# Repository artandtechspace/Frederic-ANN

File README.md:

# Frederic-ANN
Analog Neural Network

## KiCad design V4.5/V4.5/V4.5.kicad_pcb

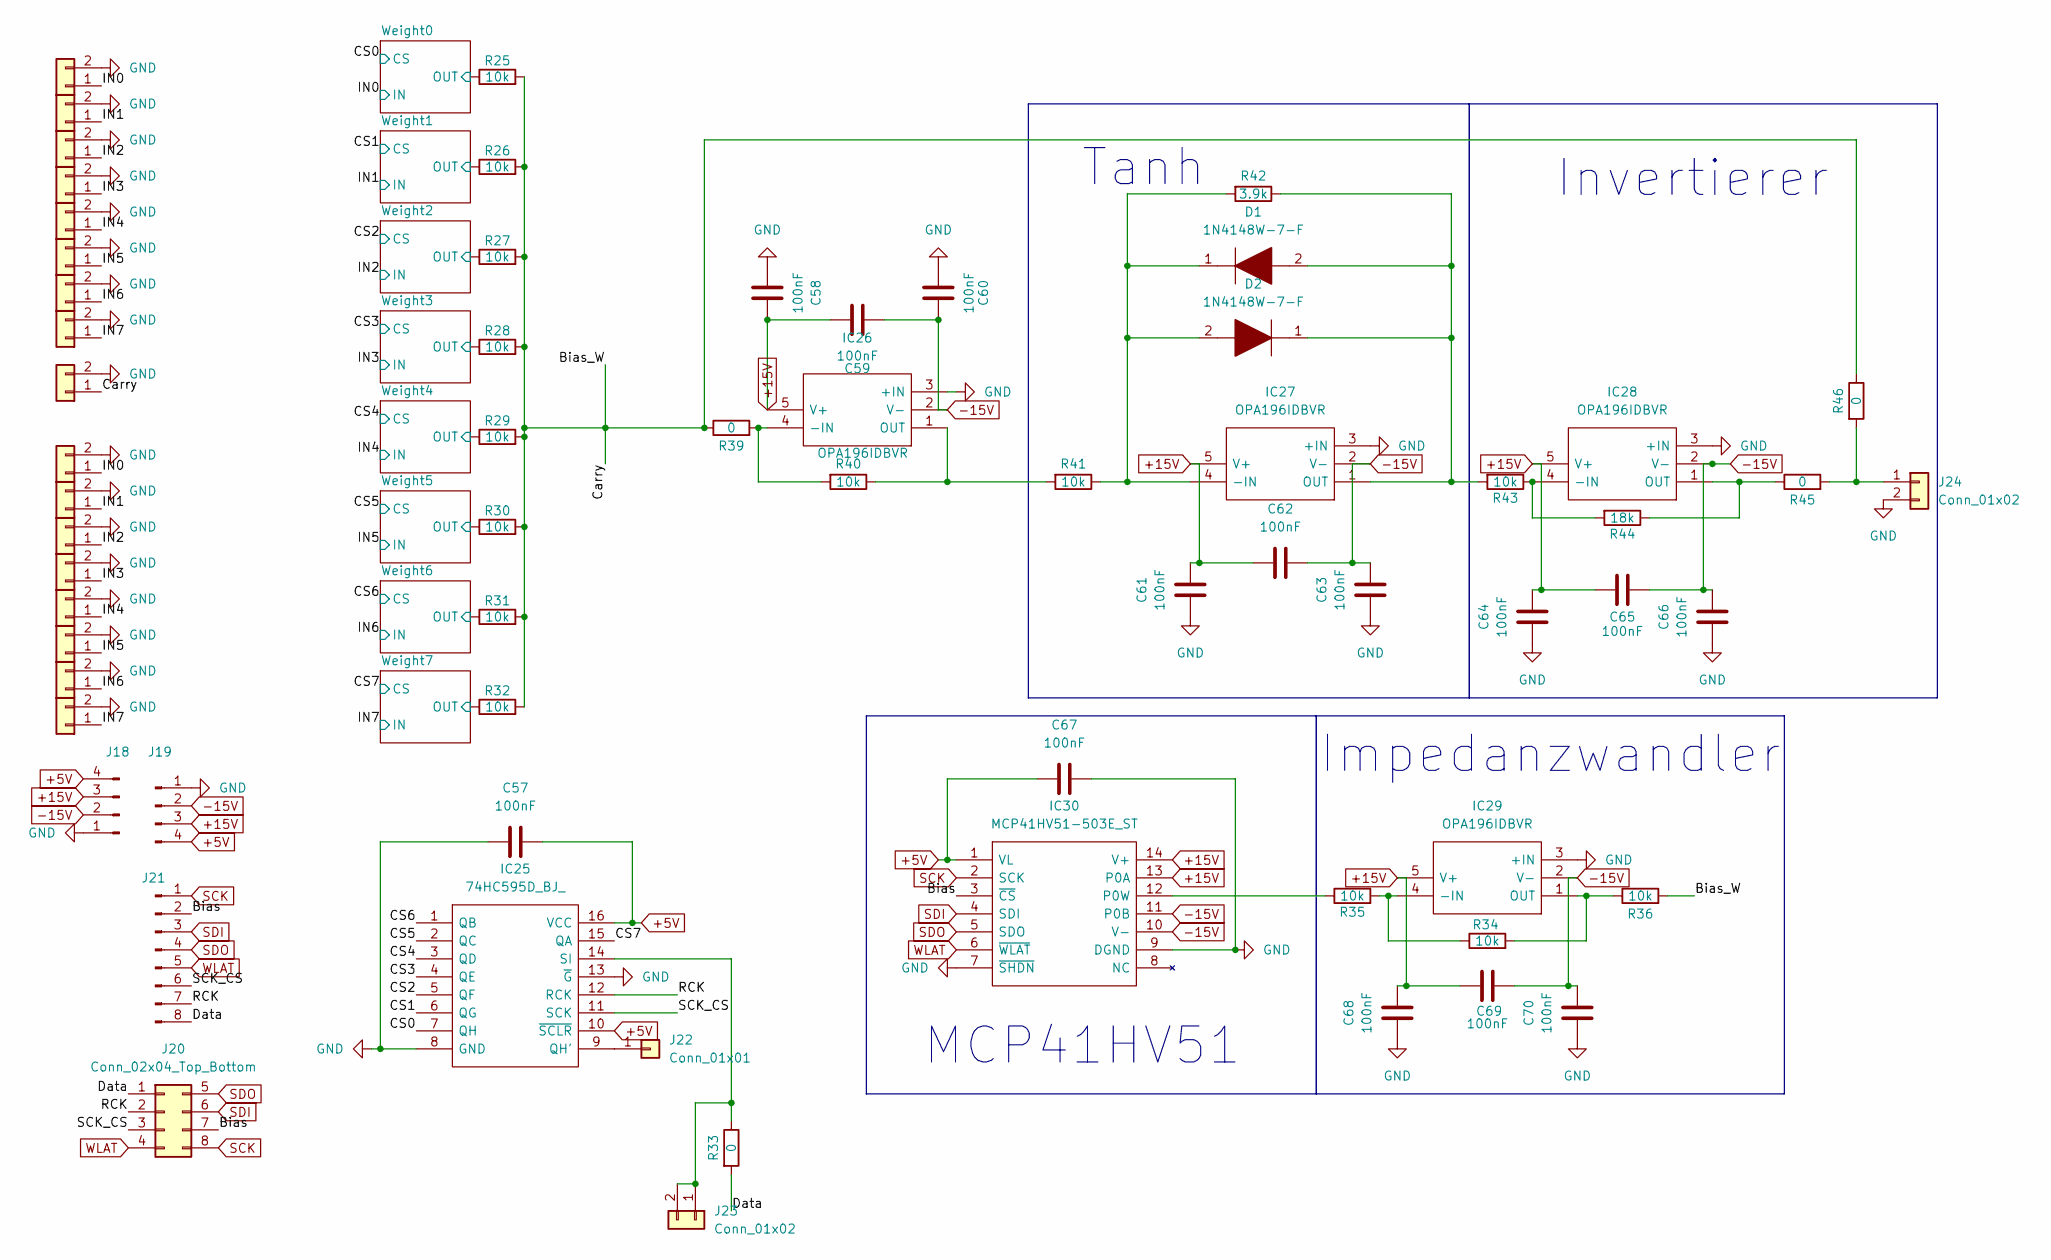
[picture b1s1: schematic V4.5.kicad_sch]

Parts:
C57, C58, C59, C60, C61, C62, C63, C64, C65, C66, C67, C68, C69, C70: 100nF; C_0805_2012Metric
D1, D2: 1N4148W-7-F; SOD3716X145N; Mouser Part Number 621-1N4148W-F
IC25: 74HC595D_BJ_; SOIC127P600X175-16N; Mouser Part Number 757-74HC595DBJ
IC26, IC27, IC28, IC29: OPA196IDBVR; SOT95P280X145-5N; Mouser Part Number 595-OPA189IDBVR
IC30: MCP41HV51-503E_ST; SOP65P640X120-14N; Mouser Part Number 579-MCP41HV51-503EST
J1, J2, J3, J4, J5, J6, J7, J8, J9, J24: Conn_01x02; JST_PH_S2B-PH-K_1x02_P2.00mm_Horizontal
J10, J11, J12, J13, J14, J15, J16, J17: Conn_01x02; PinHeader_1x02_P2.54mm_Vertical
J18: Conn_01x04_Pin; JST_PH_S4B-PH-K_1x04_P2.00mm_Horizontal
J19: Conn_01x04_Pin; PinSocket_1x04_P2.54mm_Vertical
J20: Conn_02x04_Top_Bottom; PinSocket_2x04_P2.54mm_Vertical
J21: Conn_01x08_Pin; JST_PH_S8B-PH-K_1x08_P2.00mm_Horizontal
J22: Conn_01x01; PinHeader_1x01_P2.54mm_Horizontal
J23: Conn_01x02; PinHeader_1x02_P2.54mm_Horizontal
R25, R26, R27, R28, R29, R30, R31, R32, R34, R35, R36, R40, R41, R43: 10k; R_0805_2012Metric
R33, R39, R45, R46: 0; R_0805_2012Metric
R42: 3.9k; R_0805_2012Metric
R44: 18k; R_0805_2012Metric

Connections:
+5V: C57.2, C67.1, IC25.10 (~SCLR), IC25.16 (VCC), IC30.1 (VL), J18.4, J19.4; also elsewhere on the board
+15V: C58.2, C59.2, C61.2, C62.1, C64.2, C65.1, C68.2, C69.1, IC26.5 (V+), IC27.5 (V+), IC28.5 (V+), IC29.5 (V+), IC30.13 (P0A), IC30.14 (V+), J18.3, J19.3; also elsewhere on the board
-15V: C59.1, C60.2, C62.2, C63.2, C65.2, C66.2, C69.2, C70.2, IC26.2 (V-), IC27.2 (V-), IC28.2 (V-), IC29.2 (V-), IC30.10 (V-), IC30.11 (P0B), J18.2, J19.2; also elsewhere on the board
/Bias: IC30.3 (~CS), J20.7, J21.2
/Bias_W: J9.1, R25.2, R26.2, R27.2, R28.2, R29.2, R30.2, R31.2, R32.2, R36.2, R39.1, R46.1
/CS0: IC25.7 (QH); also elsewhere on the board
/CS1: IC25.6 (QG); also elsewhere on the board
/CS2: IC25.5 (QF); also elsewhere on the board
/CS3: IC25.4 (QE); also elsewhere on the board
/CS4: IC25.3 (QD); also elsewhere on the board
/CS5: IC25.2 (QC); also elsewhere on the board
/CS6: IC25.1 (QB); also elsewhere on the board
/CS7: IC25.15 (QA); also elsewhere on the board
/Data: J20.1, J21.8, R33.2
/IN0: J1.1, J10.1; also elsewhere on the board
/IN1: J2.1, J11.1; also elsewhere on the board
/IN2: J3.1, J12.1; also elsewhere on the board
/IN3: J4.1, J13.1; also elsewhere on the board
/IN4: J5.1, J14.1; also elsewhere on the board
/IN5: J6.1, J15.1; also elsewhere on the board
/IN6: J7.1, J16.1; also elsewhere on the board
/IN7: J8.1, J17.1; also elsewhere on the board
/RCK: IC25.12 (RCK), J20.2, J21.7
/SCK_CS: IC25.11 (SCK), J20.3, J21.6
/Weight0/OUT: R25.1; also elsewhere on the board
/Weight1/OUT: R26.1; also elsewhere on the board
/Weight2/OUT: R27.1; also elsewhere on the board
/Weight3/OUT: R28.1; also elsewhere on the board
/Weight4/OUT: R29.1; also elsewhere on the board
/Weight5/OUT: R30.1; also elsewhere on the board
/Weight6/OUT: R31.1; also elsewhere on the board
/Weight7/OUT: R32.1; also elsewhere on the board
GND: C57.1, C58.1, C60.1, C61.1, C63.1, C64.1, C66.1, C67.2, C68.1, C70.1, IC25.8 (GND), IC25.13 (~G), IC26.3 (+IN), IC27.3 (+IN), IC28.3 (+IN), IC29.3 (+IN), IC30.7 (~SHDN), IC30.9 (DGND), J1.2, J2.2, J3.2, J4.2, J5.2, J6.2, J7.2, J8.2, J9.2, J10.2, J11.2, J12.2, J13.2, J14.2, J15.2, J16.2, J17.2, J18.1, J19.1, J24.2; also elsewhere on the board
unnamed: IC25.9 (QH'), J22.1
unnamed: IC25.14 (SI), J23.1, J23.2, R33.1
unnamed: IC26.4 (-IN), R39.2, R40.2
unnamed: IC26.1 (OUT), R40.1, R41.2
unnamed: D1.1, D2.2, IC27.4 (-IN), R41.1, R42.2
unnamed: D1.2, D2.1, IC27.1 (OUT), R42.1, R43.2
unnamed: IC28.4 (-IN), R43.1, R44.2
unnamed: IC28.1 (OUT), R44.1, R45.1
unnamed: IC29.4 (-IN), R34.1, R35.2
unnamed: IC29.1 (OUT), R34.2, R36.1
unnamed: IC30.12 (P0W), R35.1
unnamed: J24.1, R45.2, R46.2
SCK: IC30.2 (SCK), J20.8, J21.1; also elsewhere on the board
SDI: IC30.4 (SDI), J20.6, J21.3; also elsewhere on the board
SDO: IC30.5 (SDO), J20.5, J21.4; also elsewhere on the board
WLAT: IC30.6 (~WLAT), J20.4, J21.5; also elsewhere on the board

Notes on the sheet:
Impedanzwandler
MCP41HV51
Invertierer
Tanh

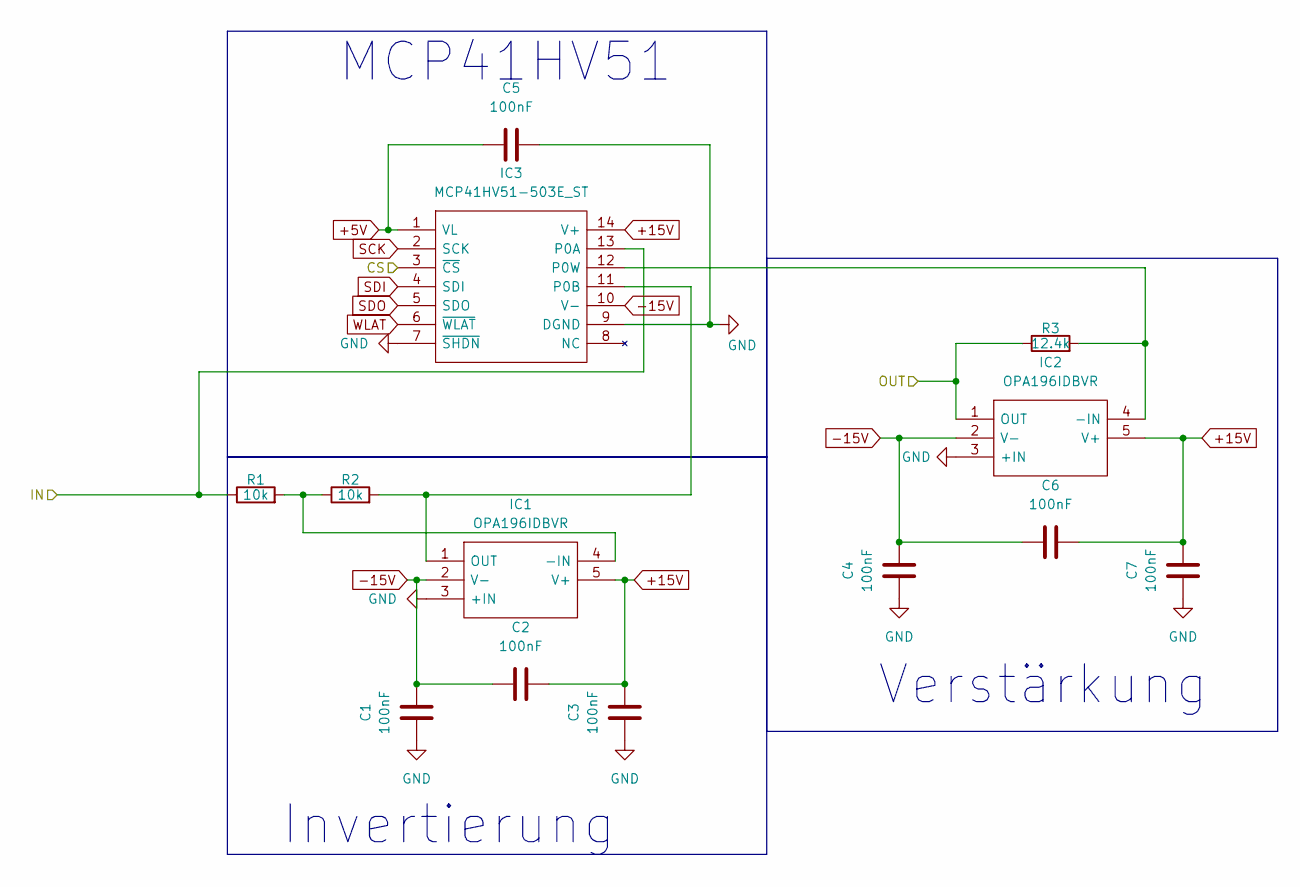
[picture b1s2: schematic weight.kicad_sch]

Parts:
C1, C2, C3, C4, C5, C6, C7: 100nF; C_0805_2012Metric
IC1, IC2: OPA196IDBVR; SOT95P280X145-5N; Mouser Part Number 595-OPA189IDBVR
IC3: MCP41HV51-503E_ST; SOP65P640X120-14N; Mouser Part Number 579-MCP41HV51-503EST
R1, R2: 10k; R_0805_2012Metric
R3: 12.4k; R_0805_2012Metric

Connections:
+5V: C5.1, IC3.1 (VL); also elsewhere on the board
+15V: C2.2, C3.2, C6.2, C7.2, IC1.5 (V+), IC2.5 (V+), IC3.14 (V+); also elsewhere on the board
-15V: C1.2, C2.1, C4.2, C6.1, IC1.2 (V-), IC2.2 (V-), IC3.10 (V-); also elsewhere on the board
/CS0: IC3.3 (~CS); also elsewhere on the board
/IN0: IC3.13 (P0A), R1.1; also elsewhere on the board
/Weight0/OUT: IC2.1 (OUT), R3.1; also elsewhere on the board
GND: C1.1, C3.1, C4.1, C5.2, C7.1, IC1.3 (+IN), IC2.3 (+IN), IC3.7 (~SHDN), IC3.9 (DGND); also elsewhere on the board
unnamed: IC1.4 (-IN), R1.2, R2.1
unnamed: IC1.1 (OUT), IC3.11 (P0B), R2.2
unnamed: IC2.4 (-IN), IC3.12 (P0W), R3.2
SCK: IC3.2 (SCK); also elsewhere on the board
SDI: IC3.4 (SDI); also elsewhere on the board
SDO: IC3.5 (SDO); also elsewhere on the board
WLAT: IC3.6 (~WLAT); also elsewhere on the board

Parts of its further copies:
C8, C9, C10, C11, C12, C13, C14, C15, C16, C17, C18, C19, C20, C21, C22, C23, C24, C25, C26, C27, C28, C29, C30, C31, C32, C33, C34, C35, C36, C37, C38, C39, C40, C41, C42, C43, C44, C45, C46, C47, C48, C49, C50, C51, C52, C53, C54, C55, C56: 100nF; C_0805_2012Metric
IC4, IC6, IC7, IC9, IC10, IC12, IC13, IC15, IC16, IC18, IC19, IC21, IC22, IC24: OPA196IDBVR; SOT95P280X145-5N; Mouser Part Number 595-OPA189IDBVR
IC5, IC8, IC11, IC14, IC17, IC20, IC23: MCP41HV51-503E_ST; SOP65P640X120-14N; Mouser Part Number 579-MCP41HV51-503EST
R4, R5, R7, R8, R10, R11, R13, R14, R16, R17, R19, R20, R22, R23: 10k; R_0805_2012Metric
R6, R9, R12, R15, R18, R21, R24: 12.4k; R_0805_2012Metric

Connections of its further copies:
+5V: C12.1, C19.1, C26.1, C33.1, C40.1, C47.1, C54.1, IC5.1 (VL), IC8.1 (VL), IC11.1 (VL), IC14.1 (VL), IC17.1 (VL), IC20.1 (VL), IC23.1 (VL); also elsewhere on the board
+15V: C9.2, C10.2, C13.2, C14.2, C16.2, C17.2, C20.2, C21.2, C23.2, C24.2, C27.2, C28.2, C30.2, C31.2, C34.2, C35.2, C37.2, C38.2, C41.2, C42.2, C44.2, C45.2, C48.2, C49.2, C51.2, C52.2, C55.2, C56.2, IC4.5 (V+), IC5.14 (V+), IC6.5 (V+), IC7.5 (V+), IC8.14 (V+), IC9.5 (V+), IC10.5 (V+), IC11.14 (V+), IC12.5 (V+), IC13.5 (V+), IC14.14 (V+), IC15.5 (V+), IC16.5 (V+), IC17.14 (V+), IC18.5 (V+), IC19.5 (V+), IC20.14 (V+), IC21.5 (V+), IC22.5 (V+), IC23.14 (V+), IC24.5 (V+); also elsewhere on the board
-15V: C8.2, C9.1, C11.2, C13.1, C15.2, C16.1, C18.2, C20.1, C22.2, C23.1, C25.2, C27.1, C29.2, C30.1, C32.2, C34.1, C36.2, C37.1, C39.2, C41.1, C43.2, C44.1, C46.2, C48.1, C50.2, C51.1, C53.2, C55.1, IC4.2 (V-), IC5.10 (V-), IC6.2 (V-), IC7.2 (V-), IC8.10 (V-), IC9.2 (V-), IC10.2 (V-), IC11.10 (V-), IC12.2 (V-), IC13.2 (V-), IC14.10 (V-), IC15.2 (V-), IC16.2 (V-), IC17.10 (V-), IC18.2 (V-), IC19.2 (V-), IC20.10 (V-), IC21.2 (V-), IC22.2 (V-), IC23.10 (V-), IC24.2 (V-); also elsewhere on the board
/CS1: IC5.3 (~CS); also elsewhere on the board
/CS2: IC8.3 (~CS); also elsewhere on the board
/CS3: IC11.3 (~CS); also elsewhere on the board
/CS4: IC14.3 (~CS); also elsewhere on the board
/CS5: IC17.3 (~CS); also elsewhere on the board
/CS6: IC20.3 (~CS); also elsewhere on the board
/CS7: IC23.3 (~CS); also elsewhere on the board
/IN1: IC5.13 (P0A), R4.1; also elsewhere on the board
/IN2: IC8.13 (P0A), R7.1; also elsewhere on the board
/IN3: IC11.13 (P0A), R10.1; also elsewhere on the board
/IN4: IC14.13 (P0A), R13.1; also elsewhere on the board
/IN5: IC17.13 (P0A), R16.1; also elsewhere on the board
/IN6: IC20.13 (P0A), R19.1; also elsewhere on the board
/IN7: IC23.13 (P0A), R22.1; also elsewhere on the board
/Weight1/OUT: IC6.1 (OUT), R6.1; also elsewhere on the board
/Weight2/OUT: IC9.1 (OUT), R9.1; also elsewhere on the board
/Weight3/OUT: IC12.1 (OUT), R12.1; also elsewhere on the board
/Weight4/OUT: IC15.1 (OUT), R15.1; also elsewhere on the board
/Weight5/OUT: IC18.1 (OUT), R18.1; also elsewhere on the board
/Weight6/OUT: IC21.1 (OUT), R21.1; also elsewhere on the board
/Weight7/OUT: IC24.1 (OUT), R24.1; also elsewhere on the board
GND: C8.1, C10.1, C11.1, C12.2, C14.1, C15.1, C17.1, C18.1, C19.2, C21.1, C22.1, C24.1, C25.1, C26.2, C28.1, C29.1, C31.1, C32.1, C33.2, C35.1, C36.1, C38.1, C39.1, C40.2, C42.1, C43.1, C45.1, C46.1, C47.2, C49.1, C50.1, C52.1, C53.1, C54.2, C56.1, IC4.3 (+IN), IC5.7 (~SHDN), IC5.9 (DGND), IC6.3 (+IN), IC7.3 (+IN), IC8.7 (~SHDN), IC8.9 (DGND), IC9.3 (+IN), IC10.3 (+IN), IC11.7 (~SHDN), IC11.9 (DGND), IC12.3 (+IN), IC13.3 (+IN), IC14.7 (~SHDN), IC14.9 (DGND), IC15.3 (+IN), IC16.3 (+IN), IC17.7 (~SHDN), IC17.9 (DGND), IC18.3 (+IN), IC19.3 (+IN), IC20.7 (~SHDN), IC20.9 (DGND), IC21.3 (+IN), IC22.3 (+IN), IC23.7 (~SHDN), IC23.9 (DGND), IC24.3 (+IN); also elsewhere on the board
unnamed: IC4.4 (-IN), R4.2, R5.1
unnamed: IC4.1 (OUT), IC5.11 (P0B), R5.2
unnamed: IC5.12 (P0W), IC6.4 (-IN), R6.2
unnamed: IC7.4 (-IN), R7.2, R8.1
unnamed: IC7.1 (OUT), IC8.11 (P0B), R8.2
unnamed: IC8.12 (P0W), IC9.4 (-IN), R9.2
unnamed: IC10.4 (-IN), R10.2, R11.1
unnamed: IC10.1 (OUT), IC11.11 (P0B), R11.2
unnamed: IC11.12 (P0W), IC12.4 (-IN), R12.2
unnamed: IC13.4 (-IN), R13.2, R14.1
unnamed: IC13.1 (OUT), IC14.11 (P0B), R14.2
unnamed: IC14.12 (P0W), IC15.4 (-IN), R15.2
unnamed: IC16.4 (-IN), R16.2, R17.1
unnamed: IC16.1 (OUT), IC17.11 (P0B), R17.2
unnamed: IC17.12 (P0W), IC18.4 (-IN), R18.2
unnamed: IC19.4 (-IN), R19.2, R20.1
unnamed: IC19.1 (OUT), IC20.11 (P0B), R20.2
unnamed: IC20.12 (P0W), IC21.4 (-IN), R21.2
unnamed: IC22.4 (-IN), R22.2, R23.1
unnamed: IC22.1 (OUT), IC23.11 (P0B), R23.2
unnamed: IC23.12 (P0W), IC24.4 (-IN), R24.2
SCK: IC5.2 (SCK), IC8.2 (SCK), IC11.2 (SCK), IC14.2 (SCK), IC17.2 (SCK), IC20.2 (SCK), IC23.2 (SCK); also elsewhere on the board
SDI: IC5.4 (SDI), IC8.4 (SDI), IC11.4 (SDI), IC14.4 (SDI), IC17.4 (SDI), IC20.4 (SDI), IC23.4 (SDI); also elsewhere on the board
SDO: IC5.5 (SDO), IC8.5 (SDO), IC11.5 (SDO), IC14.5 (SDO), IC17.5 (SDO), IC20.5 (SDO), IC23.5 (SDO); also elsewhere on the board
WLAT: IC5.6 (~WLAT), IC8.6 (~WLAT), IC11.6 (~WLAT), IC14.6 (~WLAT), IC17.6 (~WLAT), IC20.6 (~WLAT), IC23.6 (~WLAT); also elsewhere on the board

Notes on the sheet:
Verstärkung
Invertierung
MCP41HV51

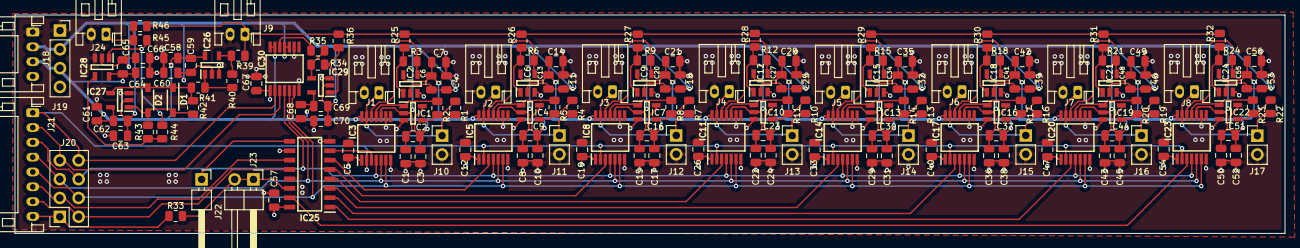
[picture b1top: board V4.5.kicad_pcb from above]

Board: 4 copper layers, 171.5 x 29.5 mm, 170 parts (0 on the bottom side), 73 nets.

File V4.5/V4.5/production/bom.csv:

Designator,Footprint,Quantity,Value,LCSC Part #
"C1, C10, C11, C12, C13, C14, C15, C16, C17, C18, C19, C2, C20, C21, C22, C23, C24, C25, C26, C27, C28, C29, C3, C30, C31, C32, C33, C34, C35, C36, C37, C38, C39, C4, C40, C41, C42, C43, C44, C45, C46, C47, C48, C49, C5, C50, C51, C52, C53, C54, C55, C56, C57, C58, C59, C6, C60, C61, C62, C63, C64, C65, C66, C67, C68, C69, C7, C70, C8, C9",0805,70,100nF,
"D1, D2",SOD3716X145N,2,1N4148W-7-F,
"IC1, IC10, IC12, IC13, IC15, IC16, IC18, IC19, IC2, IC21, IC22, IC24, IC26, IC27, IC28, IC29, IC4, IC6, IC7, IC9",SOT95P280X145-5N,20,OPA196IDBVR,
"IC11, IC14, IC17, IC20, IC23, IC3, IC30, IC5, IC8",SOP65P640X120-14N,9,MCP41HV51-503E_ST,
IC25,SOIC127P600X175-16N,1,74HC595D_BJ_,
"J1, J2, J24, J3, J4, J5, J6, J7, J8, J9",JST_PH_S2B-PH-K_1x02_P2.00mm_Horizontal,10,Conn_01x02,
"J10, J11, J12, J13, J14, J15, J16, J17",PinHeader_1x02_P2.54mm_Vertical,8,Conn_01x02,
J18,JST_PH_S4B-PH-K_1x04_P2.00mm_Horizontal,1,Conn_01x04_Pin,
J19,PinSocket_1x04_P2.54mm_Vertical,1,Conn_01x04_Pin,
J20,PinSocket_2x04_P2.54mm_Vertical,1,Conn_02x04_Top_Bottom,
J21,JST_PH_S8B-PH-K_1x08_P2.00mm_Horizontal,1,Conn_01x08_Pin,
J22,PinHeader_1x01_P2.54mm_Horizontal,1,Conn_01x01,
J23,PinHeader_1x02_P2.54mm_Horizontal,1,Conn_01x02,
"R1, R10, R11, R13, R14, R16, R17, R19, R2, R20, R22, R23, R25, R26, R27, R28, R29, R30, R31, R32, R34, R35, R36, R4, R40, R41, R43, R5, R7, R8",0805,30,10k,
"R12, R15, R18, R21, R24, R3, R6, R9",0805,8,12.4k,
"R33, R39, R45, R46",0805,4,0,
R42,0805,1,3.9k,
R44,0805,1,18k,

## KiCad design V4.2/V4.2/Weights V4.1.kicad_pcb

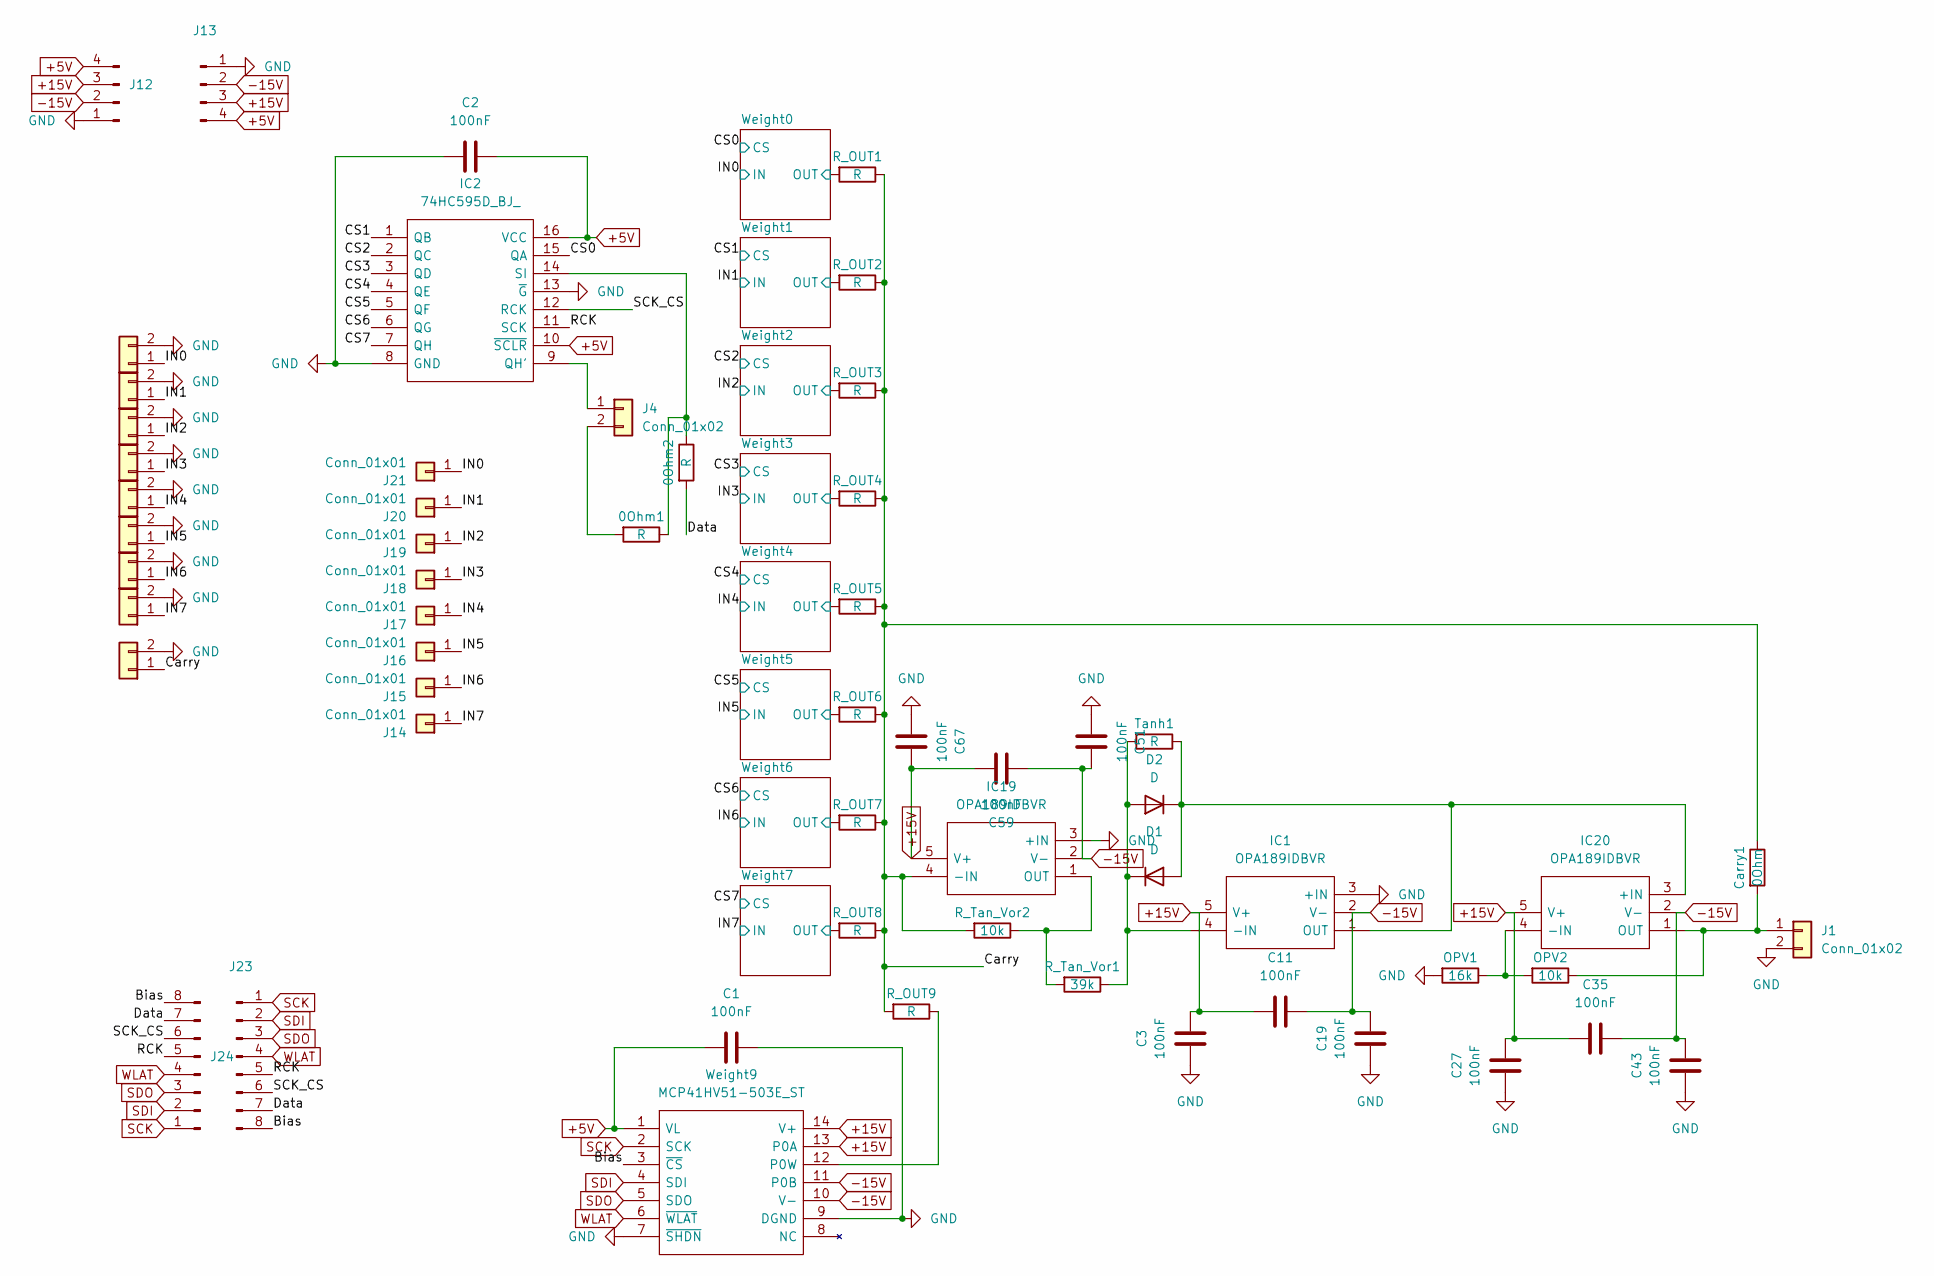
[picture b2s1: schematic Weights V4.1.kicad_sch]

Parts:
0Ohm1, 0Ohm2: R; R_0805_2012Metric
C1, C2, C3, C11, C19, C27, C35, C43, C51, C59, C67: 100nF; C_0805_2012Metric
Carry1: 0Ohm; R_0805_2012Metric
D1, D2: D; D_0805_2012Metric
IC1, IC19, IC20: OPA189IDBVR; SOT95P280X145-5N; Mouser Part Number 595-OPA189IDBVR
IC2: 74HC595D_BJ_; SOIC127P600X175-16N; Mouser Part Number 757-74HC595DBJ
J1, J2, J3, J5, J6, J7, J8, J9, J10, J11: Conn_01x02; JST_PH_S2B-PH-K_1x02_P2.00mm_Horizontal
J4: Conn_01x02; PinHeader_1x02_P2.54mm_Horizontal
J12: Conn_01x04_Pin; JST_PH_S4B-PH-K_1x04_P2.00mm_Horizontal
J13: Conn_01x04_Pin; PinHeader_1x04_P2.54mm_Vertical
J14, J15, J16, J17, J18, J19, J20, J21: Conn_01x01; PinHeader_1x01_P2.54mm_Vertical
J23: Conn_01x08_Pin; JST_PH_S8B-PH-K_1x08_P2.00mm_Horizontal
J24: Conn_01x08_Pin; PinHeader_1x08_P2.54mm_Vertical
OPV1: 16k; R_0805_2012Metric
OPV2: 10k; R_0805_2012Metric
R_OUT1, R_OUT2, R_OUT3, R_OUT4, R_OUT5, R_OUT6, R_OUT7, R_OUT8, R_OUT9: R; R_0805_2012Metric
R_Tan_Vor1: 39k; R_0805_2012Metric
R_Tan_Vor2: 10k; R_0805_2012Metric
Tanh1: R; R_0805_2012Metric
Weight9: MCP41HV51-503E_ST; SOP65P640X120-14N; Mouser Part Number 579-MCP41HV51-503EST

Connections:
+5V: C1.1, C2.2, IC2.10 (~SCLR), IC2.16 (VCC), J12.4, J13.4, Weight9.1 (VL); also elsewhere on the board
+15V: C3.2, C11.1, C27.2, C35.1, C59.2, C67.2, IC1.5 (V+), IC19.5 (V+), IC20.5 (V+), J12.3, J13.3, Weight9.13 (P0A), Weight9.14 (V+); also elsewhere on the board
-15V: C11.2, C19.2, C35.2, C43.2, C51.2, C59.1, IC1.2 (V-), IC19.2 (V-), IC20.2 (V-), J12.2, J13.2, Weight9.10 (V-), Weight9.11 (P0B); also elsewhere on the board
/Bias: J23.8, J24.8, Weight9.3 (~CS)
/CS0: IC2.15 (QA); also elsewhere on the board
/CS1: IC2.1 (QB); also elsewhere on the board
/CS2: IC2.2 (QC); also elsewhere on the board
/CS3: IC2.3 (QD); also elsewhere on the board
/CS4: IC2.4 (QE); also elsewhere on the board
/CS5: IC2.5 (QF); also elsewhere on the board
/CS6: IC2.6 (QG); also elsewhere on the board
/CS7: IC2.7 (QH); also elsewhere on the board
/Carry: Carry1.1, IC19.4 (-IN), J5.1, R_OUT1.1, R_OUT2.1, R_OUT3.1, R_OUT4.1, R_OUT5.1, R_OUT6.1, R_OUT7.1, R_OUT8.1, R_OUT9.2, R_Tan_Vor2.2
/Data: 0Ohm2.2, J23.7, J24.7
/IN0: J2.1, J21.1; also elsewhere on the board
/IN1: J3.1, J20.1; also elsewhere on the board
/IN2: J6.1, J19.1; also elsewhere on the board
/IN3: J7.1, J18.1; also elsewhere on the board
/IN4: J8.1, J17.1; also elsewhere on the board
/IN5: J9.1, J16.1; also elsewhere on the board
/IN6: J10.1, J15.1; also elsewhere on the board
/IN7: J11.1, J14.1; also elsewhere on the board
/RCK: IC2.11 (SCK), J23.5, J24.5
/SCK_CS: IC2.12 (RCK), J23.6, J24.6
/Weight0/OUT: R_OUT1.2; also elsewhere on the board
/Weight1/OUT: R_OUT2.2; also elsewhere on the board
/Weight2/OUT: R_OUT3.2; also elsewhere on the board
/Weight3/OUT: R_OUT4.2; also elsewhere on the board
/Weight4/OUT: R_OUT5.2; also elsewhere on the board
/Weight5/OUT: R_OUT6.2; also elsewhere on the board
/Weight6/OUT: R_OUT7.2; also elsewhere on the board
/Weight7/OUT: R_OUT8.2; also elsewhere on the board
GND: C1.2, C2.1, C3.1, C19.1, C27.1, C43.1, C51.1, C67.1, IC1.3 (+IN), IC2.8 (GND), IC2.13 (~G), IC19.3 (+IN), J1.2, J2.2, J3.2, J5.2, J6.2, J7.2, J8.2, J9.2, J10.2, J11.2, J12.1, J13.1, OPV1.2, Weight9.7 (~SHDN), Weight9.9 (DGND); also elsewhere on the board
unnamed: D1.2 (A), D2.1 (K), IC1.1 (OUT), IC20.3 (+IN), Tanh1.1
unnamed: D1.1 (K), D2.2 (A), IC1.4 (-IN), R_Tan_Vor1.1, Tanh1.2
unnamed: IC2.9 (QH'), J4.1
unnamed: 0Ohm1.1, 0Ohm2.1, IC2.14 (SI)
unnamed: IC19.1 (OUT), R_Tan_Vor1.2, R_Tan_Vor2.1
unnamed: IC20.4 (-IN), OPV1.1, OPV2.2
unnamed: Carry1.2, IC20.1 (OUT), J1.1, OPV2.1
unnamed: 0Ohm1.2, J4.2
unnamed: R_OUT9.1, Weight9.12 (P0W)
SCK: J23.1, J24.1, Weight9.2 (SCK); also elsewhere on the board
SDI: J23.2, J24.2, Weight9.4 (SDI); also elsewhere on the board
SDO: J23.3, J24.3, Weight9.5 (SDO); also elsewhere on the board
WLAT: J23.4, J24.4, Weight9.6 (~WLAT); also elsewhere on the board

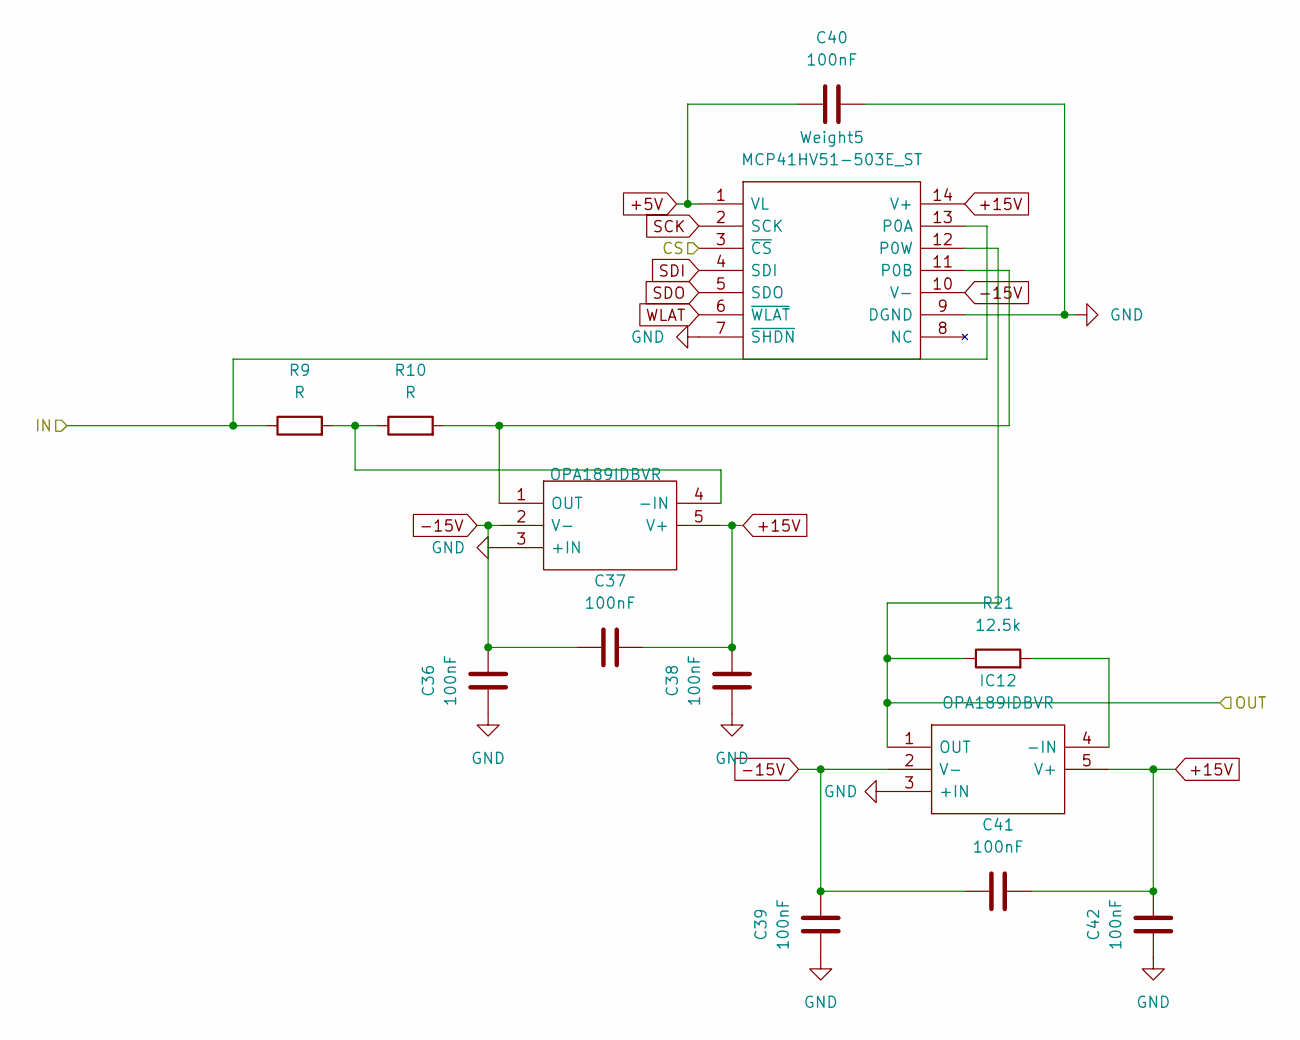
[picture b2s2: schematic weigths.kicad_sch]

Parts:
C36, C37, C38, C39, C40, C41, C42: 100nF; C_0805_2012Metric
IC11, IC12: OPA189IDBVR; SOT95P280X145-5N; Mouser Part Number 595-OPA189IDBVR
R9, R10: R; R_0805_2012Metric
R21: 12.5k; R_0805_2012Metric
Weight5: MCP41HV51-503E_ST; SOP65P640X120-14N; Mouser Part Number 579-MCP41HV51-503EST

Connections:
+5V: C40.1, Weight5.1 (VL); also elsewhere on the board
+15V: C37.2, C38.2, C41.2, C42.2, IC11.5 (V+), IC12.5 (V+), Weight5.14 (V+); also elsewhere on the board
-15V: C36.2, C37.1, C39.2, C41.1, IC11.2 (V-), IC12.2 (V-), Weight5.10 (V-); also elsewhere on the board
/CS4: Weight5.3 (~CS); also elsewhere on the board
/IN4: R9.1, Weight5.13 (P0A); also elsewhere on the board
/Weight4/OUT: IC12.1 (OUT), R21.1, Weight5.12 (P0W); also elsewhere on the board
GND: C36.1, C38.1, C39.1, C40.2, C42.1, IC11.3 (+IN), IC12.3 (+IN), Weight5.7 (~SHDN), Weight5.9 (DGND); also elsewhere on the board
unnamed: IC11.4 (-IN), R9.2, R10.1
unnamed: IC11.1 (OUT), R10.2, Weight5.11 (P0B)
unnamed: IC12.4 (-IN), R21.2
SCK: Weight5.2 (SCK); also elsewhere on the board
SDI: Weight5.4 (SDI); also elsewhere on the board
SDO: Weight5.5 (SDO); also elsewhere on the board
WLAT: Weight5.6 (~WLAT); also elsewhere on the board

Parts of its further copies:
C4, C5, C6, C7, C8, C9, C10, C12, C13, C14, C15, C16, C17, C18, C20, C21, C22, C23, C24, C25, C26, C28, C29, C30, C31, C32, C33, C34, C44, C45, C46, C47, C48, C49, C50, C52, C53, C54, C55, C56, C57, C58, C60, C61, C62, C63, C64, C65, C66: 100nF; C_0805_2012Metric
IC3, IC4, IC5, IC6, IC7, IC8, IC9, IC10, IC13, IC14, IC15, IC16, IC17, IC18: OPA189IDBVR; SOT95P280X145-5N; Mouser Part Number 595-OPA189IDBVR
R1, R2, R3, R4, R5, R6, R7, R8, R11, R12, R13, R14, R15, R16: R; R_0805_2012Metric
R17, R18, R19, R20, R22, R23, R24: 12.5k; R_0805_2012Metric
Weight1, Weight2, Weight3, Weight4, Weight6, Weight7, Weight8: MCP41HV51-503E_ST; SOP65P640X120-14N; Mouser Part Number 579-MCP41HV51-503EST

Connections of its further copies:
+5V: C8.1, C16.1, C24.1, C32.1, C48.1, C56.1, C64.1, Weight1.1 (VL), Weight2.1 (VL), Weight3.1 (VL), Weight4.1 (VL), Weight6.1 (VL), Weight7.1 (VL), Weight8.1 (VL); also elsewhere on the board
+15V: C5.2, C6.2, C9.2, C10.2, C13.2, C14.2, C17.2, C18.2, C21.2, C22.2, C25.2, C26.2, C29.2, C30.2, C33.2, C34.2, C45.2, C46.2, C49.2, C50.2, C53.2, C54.2, C57.2, C58.2, C61.2, C62.2, C65.2, C66.2, IC3.5 (V+), IC4.5 (V+), IC5.5 (V+), IC6.5 (V+), IC7.5 (V+), IC8.5 (V+), IC9.5 (V+), IC10.5 (V+), IC13.5 (V+), IC14.5 (V+), IC15.5 (V+), IC16.5 (V+), IC17.5 (V+), IC18.5 (V+), Weight1.14 (V+), Weight2.14 (V+), Weight3.14 (V+), Weight4.14 (V+), Weight6.14 (V+), Weight7.14 (V+), Weight8.14 (V+); also elsewhere on the board
-15V: C4.2, C5.1, C7.2, C9.1, C12.2, C13.1, C15.2, C17.1, C20.2, C21.1, C23.2, C25.1, C28.2, C29.1, C31.2, C33.1, C44.2, C45.1, C47.2, C49.1, C52.2, C53.1, C55.2, C57.1, C60.2, C61.1, C63.2, C65.1, IC3.2 (V-), IC4.2 (V-), IC5.2 (V-), IC6.2 (V-), IC7.2 (V-), IC8.2 (V-), IC9.2 (V-), IC10.2 (V-), IC13.2 (V-), IC14.2 (V-), IC15.2 (V-), IC16.2 (V-), IC17.2 (V-), IC18.2 (V-), Weight1.10 (V-), Weight2.10 (V-), Weight3.10 (V-), Weight4.10 (V-), Weight6.10 (V-), Weight7.10 (V-), Weight8.10 (V-); also elsewhere on the board
/CS0: Weight1.3 (~CS); also elsewhere on the board
/CS1: Weight2.3 (~CS); also elsewhere on the board
/CS2: Weight3.3 (~CS); also elsewhere on the board
/CS3: Weight4.3 (~CS); also elsewhere on the board
/CS5: Weight6.3 (~CS); also elsewhere on the board
/CS6: Weight7.3 (~CS); also elsewhere on the board
/CS7: Weight8.3 (~CS); also elsewhere on the board
/IN0: R1.1, Weight1.13 (P0A); also elsewhere on the board
/IN1: R3.1, Weight2.13 (P0A); also elsewhere on the board
/IN2: R5.1, Weight3.13 (P0A); also elsewhere on the board
/IN3: R7.1, Weight4.13 (P0A); also elsewhere on the board
/IN5: R11.1, Weight6.13 (P0A); also elsewhere on the board
/IN6: R13.1, Weight7.13 (P0A); also elsewhere on the board
/IN7: R15.1, Weight8.13 (P0A); also elsewhere on the board
/Weight0/OUT: IC4.1 (OUT), R17.1, Weight1.12 (P0W); also elsewhere on the board
/Weight1/OUT: IC6.1 (OUT), R18.1, Weight2.12 (P0W); also elsewhere on the board
/Weight2/OUT: IC8.1 (OUT), R19.1, Weight3.12 (P0W); also elsewhere on the board
/Weight3/OUT: IC10.1 (OUT), R20.1, Weight4.12 (P0W); also elsewhere on the board
/Weight5/OUT: IC14.1 (OUT), R22.1, Weight6.12 (P0W); also elsewhere on the board
/Weight6/OUT: IC16.1 (OUT), R23.1, Weight7.12 (P0W); also elsewhere on the board
/Weight7/OUT: IC18.1 (OUT), R24.1, Weight8.12 (P0W); also elsewhere on the board
GND: C4.1, C6.1, C7.1, C8.2, C10.1, C12.1, C14.1, C15.1, C16.2, C18.1, C20.1, C22.1, C23.1, C24.2, C26.1, C28.1, C30.1, C31.1, C32.2, C34.1, C44.1, C46.1, C47.1, C48.2, C50.1, C52.1, C54.1, C55.1, C56.2, C58.1, C60.1, C62.1, C63.1, C64.2, C66.1, IC3.3 (+IN), IC4.3 (+IN), IC5.3 (+IN), IC6.3 (+IN), IC7.3 (+IN), IC8.3 (+IN), IC9.3 (+IN), IC10.3 (+IN), IC13.3 (+IN), IC14.3 (+IN), IC15.3 (+IN), IC16.3 (+IN), IC17.3 (+IN), IC18.3 (+IN), Weight1.7 (~SHDN), Weight1.9 (DGND), Weight2.7 (~SHDN), Weight2.9 (DGND), Weight3.7 (~SHDN), Weight3.9 (DGND), Weight4.7 (~SHDN), Weight4.9 (DGND), Weight6.7 (~SHDN), Weight6.9 (DGND), Weight7.7 (~SHDN), Weight7.9 (DGND), Weight8.7 (~SHDN), Weight8.9 (DGND); also elsewhere on the board
unnamed: IC3.4 (-IN), R1.2, R2.1
unnamed: IC3.1 (OUT), R2.2, Weight1.11 (P0B)
unnamed: IC4.4 (-IN), R17.2
unnamed: IC5.4 (-IN), R3.2, R4.1
unnamed: IC5.1 (OUT), R4.2, Weight2.11 (P0B)
unnamed: IC6.4 (-IN), R18.2
unnamed: IC7.4 (-IN), R5.2, R6.1
unnamed: IC7.1 (OUT), R6.2, Weight3.11 (P0B)
unnamed: IC8.4 (-IN), R19.2
unnamed: IC9.4 (-IN), R7.2, R8.1
unnamed: IC9.1 (OUT), R8.2, Weight4.11 (P0B)
unnamed: IC10.4 (-IN), R20.2
unnamed: IC13.4 (-IN), R11.2, R12.1
unnamed: IC13.1 (OUT), R12.2, Weight6.11 (P0B)
unnamed: IC14.4 (-IN), R22.2
unnamed: IC15.4 (-IN), R13.2, R14.1
unnamed: IC15.1 (OUT), R14.2, Weight7.11 (P0B)
unnamed: IC16.4 (-IN), R23.2
unnamed: IC17.4 (-IN), R15.2, R16.1
unnamed: IC17.1 (OUT), R16.2, Weight8.11 (P0B)
unnamed: IC18.4 (-IN), R24.2
SCK: Weight1.2 (SCK), Weight2.2 (SCK), Weight3.2 (SCK), Weight4.2 (SCK), Weight6.2 (SCK), Weight7.2 (SCK), Weight8.2 (SCK); also elsewhere on the board
SDI: Weight1.4 (SDI), Weight2.4 (SDI), Weight3.4 (SDI), Weight4.4 (SDI), Weight6.4 (SDI), Weight7.4 (SDI), Weight8.4 (SDI); also elsewhere on the board
SDO: Weight1.5 (SDO), Weight2.5 (SDO), Weight3.5 (SDO), Weight4.5 (SDO), Weight6.5 (SDO), Weight7.5 (SDO), Weight8.5 (SDO); also elsewhere on the board
WLAT: Weight1.6 (~WLAT), Weight2.6 (~WLAT), Weight3.6 (~WLAT), Weight4.6 (~WLAT), Weight6.6 (~WLAT), Weight7.6 (~WLAT), Weight8.6 (~WLAT); also elsewhere on the board

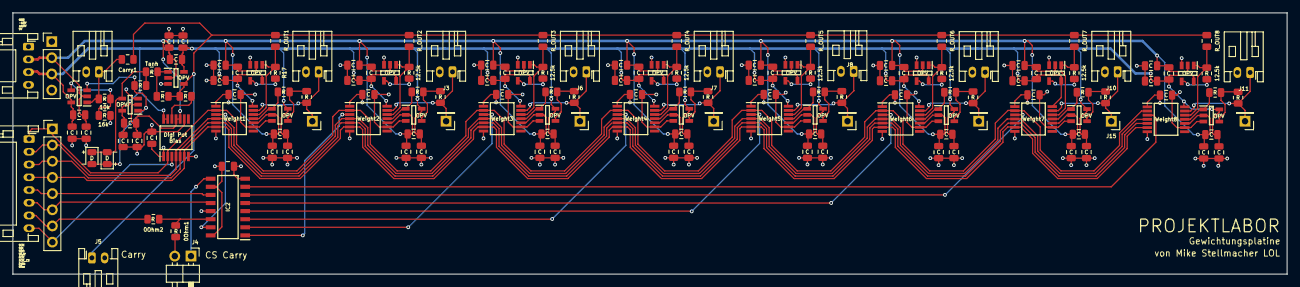
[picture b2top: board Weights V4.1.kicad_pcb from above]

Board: 4 copper layers, 200.0 x 41.0 mm, 162 parts (0 on the bottom side), 70 nets.

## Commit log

2025-01-13 V4.5
2025-01-13 KiCad Libs
2025-01-13 Nothing
